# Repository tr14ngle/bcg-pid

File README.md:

# Digitally tuned analog PID controller for BCG system

## Overview

This repository contains KiCad files, as well as some LTSpice simulations for an experimental digitally tuned PID controller. The controller is designed to be part of a ballistocardiography (BCG) measuring system. In BCG, the function of the heart is measured by th forces caused by movement of the blood as a result of heartbeat. This is in contrast to better known electrocardiography (ECG), where heart function is assessed by measuring electrical signals. Compared to ECG, where the shape of the waveform is more important, in BCG the amplitude of the BCG signal carries important information about the heart's condition. Because BCG measures physical force, the patient's mass, among other things, can influence the amplitude of the signal. This makes long-term measurements difficult because the patient's weight and other affecting factors often vary over time. 

This PID controller is a continuation of a project completed Aalto University's Automation and Electrical Engineering Master Programme's Project Work course ([link to project folder](https://wiki.aalto.fi/display/AEEproject/Instrumentation+for+Ballistocardiography+2023?searchId=NLV66OIGJ)). Over the course, a system was implemented where the patient lays on suspended frame. The motion of the suspended frame can be controlled using two solenoids. A load cell is used to measure the position of the frame and a PID controller then controls the solenoids in such a way that the bed frame is kept stationary. This way, when the patient lays motionless, the BCG signal can be aquired from the control signals of the solenoids. This approach keeps the patient's body stationary, effectively canceling body inertia, which normalizes the resultant BCG signal. During the course, an unconventional, analogic PID controller was implemented. The controller was manually tuned using potentiometer which proved unfeasible, as manual tuning was quite diffictult and necessary for each measurement. This project attempts to address this by implementing digital tuning of the P, I and D blocks using digital potentiometers.

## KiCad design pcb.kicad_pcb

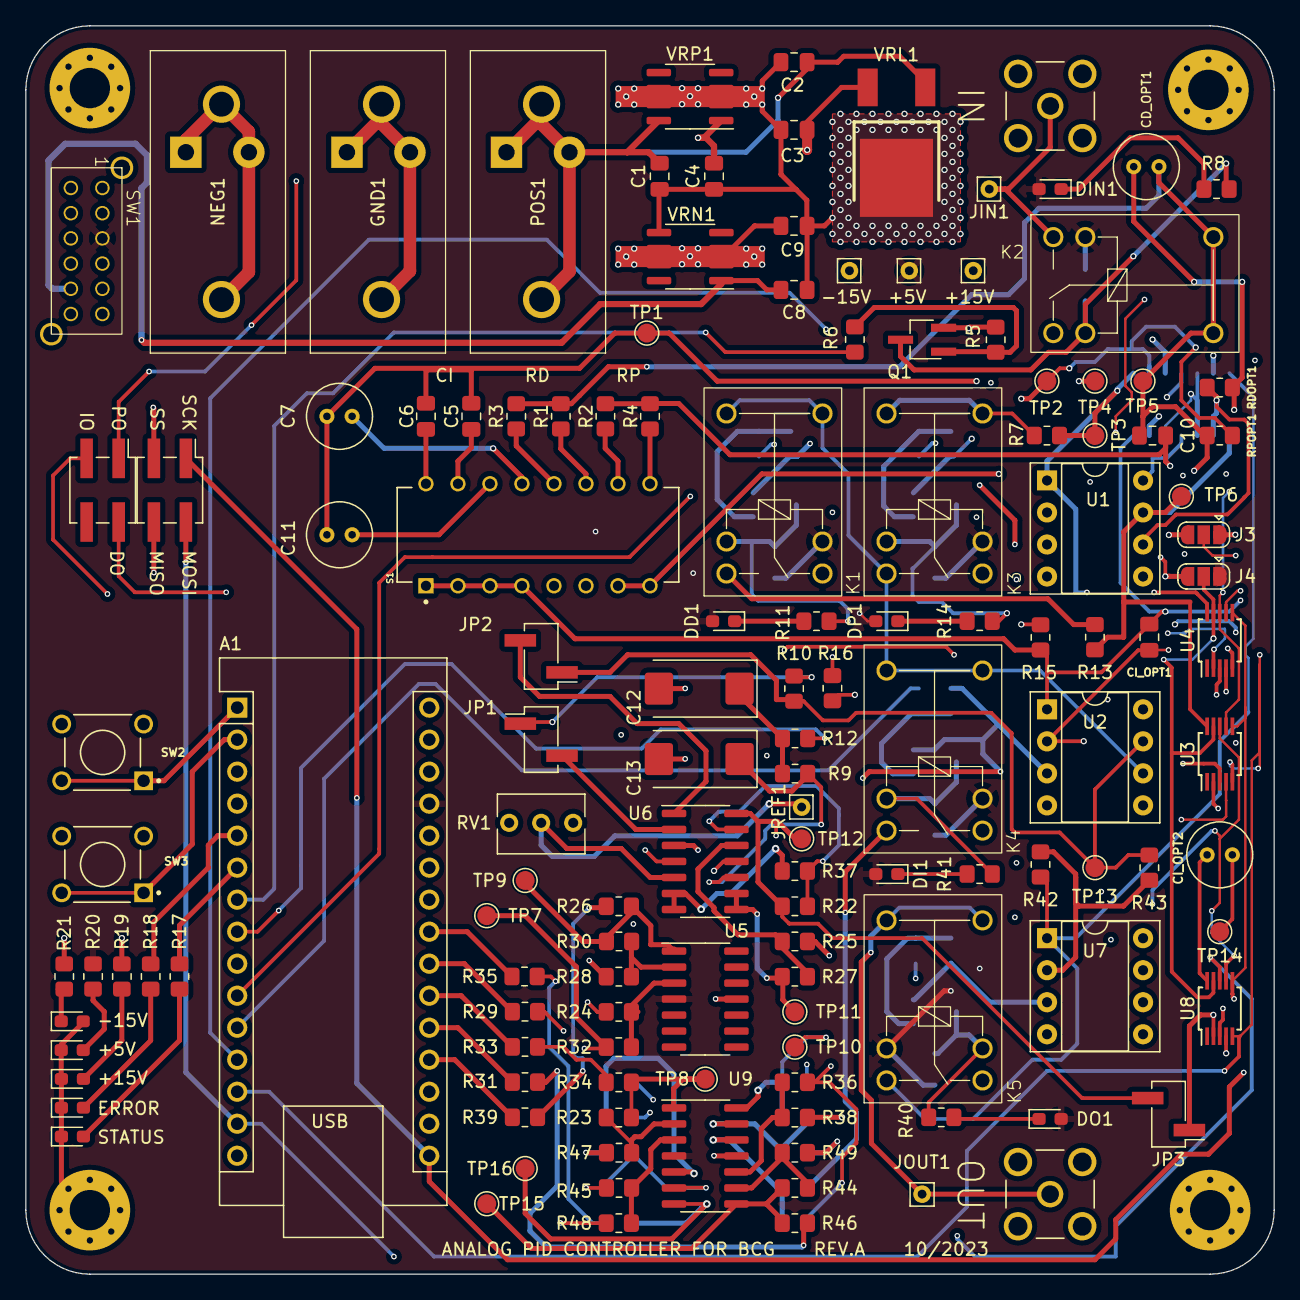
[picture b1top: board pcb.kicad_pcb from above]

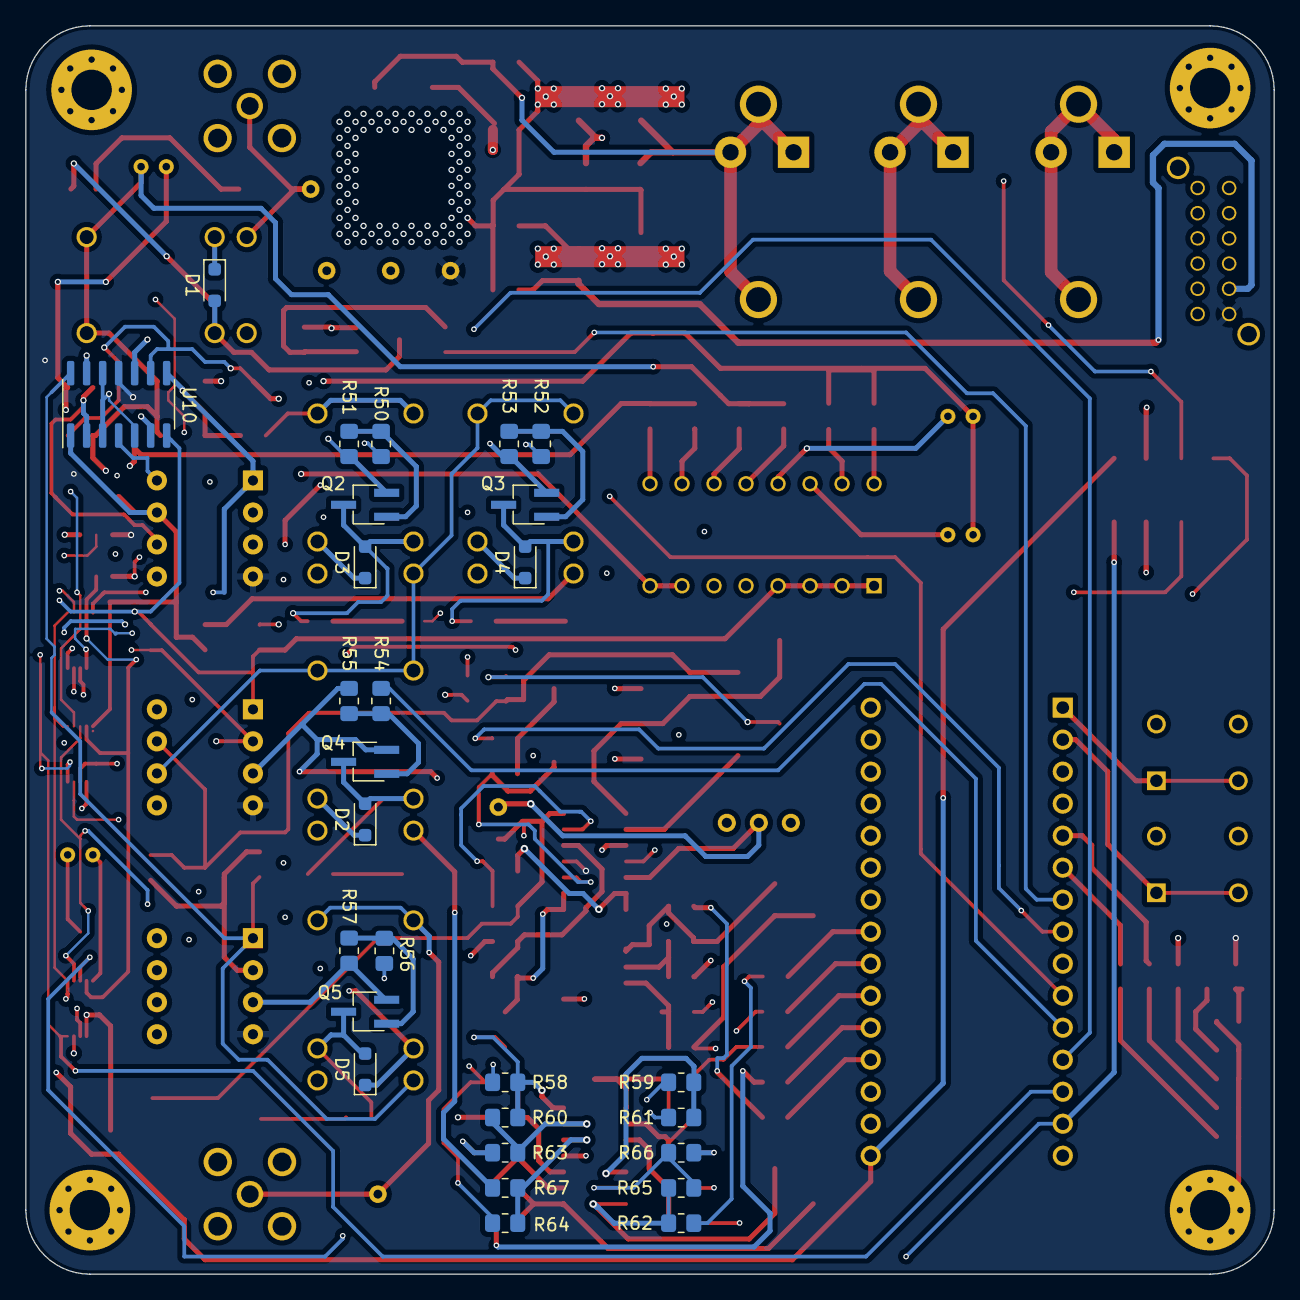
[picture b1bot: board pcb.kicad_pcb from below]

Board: 4 copper layers, 99.1 x 99.1 mm, 170 parts (28 on the bottom side), 109 nets.

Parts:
+1, +2: Conn_01x01_Pin; Pin_D0.7mm_L6.5mm_W1.8mm_FlatFork
-1: Conn_01x01_Pin; Pin_D0.7mm_L6.5mm_W1.8mm_FlatFork
A1: Arduino_Nano_v3.x; Arduino_Nano
C1, C2, C9: 0.33u; C_0805_2012Metric_Pad1.18x1.45mm_HandSolder
C3, C4, C8, C10: 0.1u; C_0805_2012Metric_Pad1.18x1.45mm_HandSolder
C5, C6: C; C_0805_2012Metric_Pad1.18x1.45mm_HandSolder
C7, C11: C; C_Radial_D5.0mm_H5.0mm_P2.00mm
C12, C13: 10u; CP_EIA-7343-40_Kemet-Y_Pad2.25x2.55mm_HandSolder
CD_OPT1: C; C_Radial_D5.0mm_H5.0mm_P2.00mm
CI_OPT1: C; C_0805_2012Metric_Pad1.18x1.45mm_HandSolder
CI_OPT2: C; C_Radial_D5.0mm_H5.0mm_P2.00mm
D1, D2, D3, D4, D5: D; D_SOD-323_HandSoldering
DD1: LED; LED_0603_1608Metric_Pad1.05x0.95mm_HandSolder
DERROR1: LED; LED_0603_1608Metric_Pad1.05x0.95mm_HandSolder
DI1: LED; LED_0603_1608Metric_Pad1.05x0.95mm_HandSolder
DIN1: LED; LED_0603_1608Metric_Pad1.05x0.95mm_HandSolder
DLOG1: LED; LED_0603_1608Metric_Pad1.05x0.95mm_HandSolder
DNEG1: LED; LED_0603_1608Metric_Pad1.05x0.95mm_HandSolder
DO1: LED; LED_0603_1608Metric_Pad1.05x0.95mm_HandSolder
DP1: LED; LED_0603_1608Metric_Pad1.05x0.95mm_HandSolder
DPOS1: LED; LED_0603_1608Metric_Pad1.05x0.95mm_HandSolder
DSTATUS1: LED; LED_0603_1608Metric_Pad1.05x0.95mm_HandSolder
GND1: 24.243.1; 242431
GND_OPT1: Screw_Terminal_01x02; TerminalBlock_RND_205-00276_1x02_P5.00mm_Vertical
H1, H2, H3, H4: MountingHole_Pad; MountingHole_3.2mm_M3_Pad_Via
IN: CONSMA002; LINX_CONSMA002
J1, J2: Conn_02x02_Top_Bottom; PinHeader_2x02_P2.54mm_Vertical_SMD
J3, J4: Conn_01x03_Pin; SolderJumper-3_P1.3mm_Open_RoundedPad1.0x1.5mm
JIN1: Conn_01x01_Pin; Pin_D0.7mm_L6.5mm_W1.8mm_FlatFork
JOUT1: Conn_01x01_Pin; Pin_D0.7mm_L6.5mm_W1.8mm_FlatFork
JP1, JP2, JP3: Jumper_2_Open; PinHeader_1x02_P2.54mm_Vertical_SMD_Pin1Left
JREF1: Conn_01x01_Pin; Pin_D0.7mm_L6.5mm_W1.8mm_FlatFork
K1, K2, K3, K4, K5: SRS-3V
NEG1: 24.243.1; 242431
NEG_OPT1: Screw_Terminal_01x02; TerminalBlock_RND_205-00276_1x02_P5.00mm_Vertical
OUT: CONSMA002; LINX_CONSMA002
POS1: 24.243.1; 242431
POS_OPT1: Screw_Terminal_01x02; TerminalBlock_RND_205-00276_1x02_P5.00mm_Vertical
Q1, Q2, Q3, Q4, Q5: NMOS; TSOT-23_HandSoldering
R1, R2, R3, R4: R; R_0805_2012Metric_Pad1.20x1.40mm_HandSolder
R5, R51, R53, R55, R57: 47k; R_0805_2012Metric_Pad1.20x1.40mm_HandSolder
R6, R50, R52, R54, R56: 470; R_0805_2012Metric_Pad1.20x1.40mm_HandSolder
R7, R10, R13, R15, R42, R43: 10k; R_0805_2012Metric_Pad1.20x1.40mm_HandSolder
R8, R11, R14, R16, R17, R18, R20, R29, R31, R33, R35, R39, R40, R41: 330; R_0805_2012Metric_Pad1.20x1.40mm_HandSolder
R9, R12: 68; R_0805_2012Metric_Pad1.20x1.40mm_HandSolder
R19, R21: 1.2k; R_0805_2012Metric_Pad1.20x1.40mm_HandSolder
R22, R25, R26, R28, R32, R34, R38, R46, R47, R48, R49, R58, R61, R62, R63, R66, R67: 100k; R_0805_2012Metric_Pad1.20x1.40mm_HandSolder
R23, R24, R30, R36, R44, R45, R59, R60, R64, R65: 15k; R_0805_2012Metric_Pad1.20x1.40mm_HandSolder
R27, R37: 18k; R_0805_2012Metric_Pad1.20x1.40mm_HandSolder
RDOPT1: 10k; R_0805_2012Metric_Pad1.20x1.40mm_HandSolder
RPOPT1: 10k; R_0805_2012Metric_Pad1.20x1.40mm_HandSolder
RV1: 100k; Potentiometer_Bourns_3266Y_Vertical
S1: ADE0804; SW_ADE0804
SW1: EG4208
SW2, SW3: 1825910-6; SW_1825910-6-4
TP1, TP2, TP3, TP4, TP5, TP6, TP7, TP8, TP9, TP10, TP11, TP12, TP13, TP14, TP15, TP16: TestPoint; TestPoint_Pad_D1.5mm
U1, U2, U7: LM358; DIP-8_W7.62mm_Socket
U3, U4, U8: AD5290; MSOP-10_3x3mm_P0.5mm
U5, U6, U9, U10: NCS20074D; SOIC-14_3.9x8.7mm_P1.27mm
VRL1: NCV7805BDTRKG; NCV7805BDTRKG_1
VRN1: MC79L15_SO8; SOIC-8_3.9x4.9mm_P1.27mm
VRP1: MC78L15_SO8; SOIC-8_3.9x4.9mm_P1.27mm

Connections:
2.5V: JREF1.1, R24.1, R36.1, R45.1, R59.1, R64.1, RV1.2, U6.5 (+)
+5V: +2.1, A1.27 (+5V), D1.1 (K), D2.1 (K), D3.1 (K), D4.1 (K), D5.1 (K), DD1.2 (A), DI1.2 (A), DIN1.2 (A), DO1.2 (A), DP1.2 (A), J4.1, K1.3, K2.4, K3.3, K4.3, K5.4, R20.2, SW1.3, U5.4 (V+), U9.4 (V+)
+15V: +1.1, J4.3, R19.2, SW1.6, U1.8 (V+), U2.8 (V+), U6.4 (V+), U7.8 (V+), U10.4 (V+)
-15V: -1.1, J3.3, R21.2, SW1.12, U1.4 (V-), U2.4 (V-), U6.11 (V-), U7.4 (V-), U10.11 (V-)
/Ci1: C5.1, C6.1, C7.1, C11.1, CI_OPT1.1, CI_OPT2.1, TP1.1, U2.2 (-), U8.10 (RW), U10.6 (-)
/Ci2: CI_OPT1.2, CI_OPT2.2, R15.1, S1.1, S1.2, S1.3, S1.4, TP14.1, U2.1, U10.7
/K1D: D3.2 (A), K3.4, Q2.1 (D), R14.1
/K2D: D2.2 (A), K4.4, Q4.1 (D), R41.1
/K3D: D4.2 (A), K1.4, Q3.1 (D), R11.1
/K4D: D5.2 (A), K5.3, Q5.1 (D), R40.1
/K5D: D1.2 (A), K2.3, Q1.1 (D), R8.1
/Rd1: C10.2, CD_OPT1.2, R2.2, R4.2, RDOPT1.1
/Rd2: RDOPT1.2, S1.7, S1.8, TP4.1, U1.6 (-), U3.2 (RL), U10.2 (-)
/Rp1: C10.1, CD_OPT1.1, JP3.1 (A), K2.5, K2.6, R1.2, R3.2, R38.1, RPOPT1.1, TP5.1, U8.2 (RL)
/Rp2: RPOPT1.2, S1.5, S1.6, TP2.1, U1.2 (-), U4.2 (RL), U10.9 (-)
/control_out: A1.8 (D5), R12.2
/der_out: R13.1, TP6.1, U1.7, U3.10 (RW), U10.1
/inv_in: R42.1, R43.2, U7.2 (-), U10.13 (-)
/inv_out: K5.1, R32.1, R42.2, TP7.1, U7.1, U10.14
/potvdd: J4.2, U3.9 (Vdd+), U4.9 (Vdd+), U8.9 (Vdd+)
/potvss: J3.2, U3.3 (Vss-), U4.3 (Vss-), U8.3 (Vss-)
/prop_out: R7.1, TP3.1, U1.1, U4.10 (RW), U10.8
/sig_d: K1.1, R13.2, R61.1
/sig_i: K4.1, R15.2, R67.1
/sig_p: K3.5, K3.6, R7.2, R48.1
/sum_in: JP1.1 (A), K1.5, K1.6, K3.1, K4.5, K4.6, R10.1, U2.6 (-)
/sum_out: JP2.1 (A), R10.2, R43.1, TP13.1, U2.7
DO: J2.2, U3.8 (SDO), U8.7 (SDI)
GND: A1.4 (GND), A1.29 (GND), C1.1, C2.1, C3.1, C4.1, C8.2, C9.2, C12.2, C13.2, DERROR1.1 (K), DLOG1.1 (K), DNEG1.2 (A), DPOS1.1 (K), DSTATUS1.1 (K), GND1.1, GND1.2, GND_OPT1.1, GND_OPT1.2, H1.1, H2.1, H3.1, H4.1, IN.S1, IN.S2, IN.S3, IN.S4, J3.1, OUT.S1, OUT.S2, OUT.S3, OUT.S4, Q1.3 (S), Q2.3 (S), Q3.3 (S), Q4.3 (S), Q5.3 (S), R5.1, R25.1, R28.1, R47.1, R49.1, R51.1, R53.1, R55.1, R57.1, R63.1, R66.1, RV1.3, SW1.13 (GND), SW1.14 (GND), SW2.3, SW2.4, SW3.3, SW3.4, U1.3 (+), U1.5 (+), U2.3 (+), U2.5 (+), U3.4 (GND), U4.4 (GND), U5.11 (V-), U6.3 (+), U7.3 (+), U8.4 (GND), U9.11 (V-), U10.3 (+), U10.5 (+), U10.10 (+), U10.12 (+), VRL1.3 (GROUND), VRN1.5 (GND), VRP1.2 (GND), VRP1.3 (GND), VRP1.6 (GND), VRP1.7 (GND)
IO: J2.3, U8.8 (SDO)
MISO: A1.15 (D12), J1.4
MOSI: A1.14 (D11), J1.2, U4.7 (SDI)
unnamed: A1.19 (A0), R39.1
unnamed: A1.20 (A1), R31.2
unnamed: A1.21 (A2), R33.2
unnamed: A1.22 (A3), R29.2
unnamed: A1.23 (A4), R35.2
unnamed: A1.2 (D0/RX), SW3.1, SW3.2
unnamed: A1.1 (D1/TX), SW2.1, SW2.2
unnamed: A1.5 (D2), R18.2
unnamed: A1.6 (D3), R17.2
unnamed: A1.7 (D4), R6.2
unnamed: A1.9 (D6), R56.2
unnamed: A1.10 (D7), R52.2
unnamed: A1.11 (D8), R54.2
unnamed: A1.12 (D9), R50.2
unnamed: C6.2, S1.1-1
unnamed: C5.2, S1.2-1
unnamed: C11.2, S1.3-1
unnamed: C7.2, S1.4-1
unnamed: C12.1, R9.2, R12.1
unnamed: DD1.1 (K), R11.2
unnamed: DERROR1.2 (A), R18.1
unnamed: DI1.1 (K), R41.2
unnamed: DIN1.1 (K), R8.2
unnamed: DLOG1.2 (A), R20.1
unnamed: DNEG1.1 (K), R21.1
unnamed: DO1.1 (K), R40.2
unnamed: DP1.1 (K), R14.2
unnamed: DPOS1.2 (A), R19.1
unnamed: DSTATUS1.2 (A), R17.1
unnamed: IN.1, JIN1.1, K2.1
unnamed: R37.2, U6.6 (-), U6.7
unnamed: JOUT1.1, K5.5, K5.6, OUT.1
unnamed: JP1.2 (B), U6.2 (-)
unnamed: JP2.2 (B), U6.1
unnamed: JP3.2 (B), R16.1, R22.1, TP12.1, U6.14
unnamed: K2.2, R16.2
unnamed: C9.1, NEG1.1, NEG1.2, NEG_OPT1.1, NEG_OPT1.2, VRN1.2 (IN), VRN1.3 (IN), VRN1.6 (IN), VRN1.7 (IN)
unnamed: C1.2, C2.2, POS1.1, POS1.2, POS_OPT1.1, POS_OPT1.2, VRL1.1 (INPUT), VRP1.8 (IN)
unnamed: Q2.2 (G), R50.1, R51.2
unnamed: Q4.2 (G), R54.1, R55.2
unnamed: Q3.2 (G), R52.1, R53.2
unnamed: Q5.2 (G), R56.1, R57.2
unnamed: Q1.2 (G), R5.2, R6.1
unnamed: R1.1, S1.6-1
unnamed: R3.1, S1.5-1
unnamed: R2.1, S1.7-1
unnamed: R4.1, S1.8-1
unnamed: R23.1, R34.1, TP8.1, U9.1
unnamed: R26.2, R39.2
unnamed: R31.1, R46.2
unnamed: R33.1, R34.2
unnamed: R29.1, R58.2
unnamed: R35.1, R62.2
unnamed: R44.1, R46.1, TP15.1, U9.8
unnamed: R62.1, R65.1, TP16.1, U9.7
unnamed: R58.1, R60.1, TP10.1, U9.14
unnamed: R26.1, R30.1, TP9.1, U5.1
unnamed: C13.1, R9.1, U6.10 (+)
unnamed: R27.2, TP11.1, U6.8, U6.9 (-)
unnamed: R25.2, R27.1, U6.12 (+)
unnamed: R22.2, R37.1, U6.13 (-)
unnamed: R45.2, R48.2, U9.3 (+)
unnamed: R23.2, R47.2, U9.2 (-)
unnamed: R59.2, R61.2, U9.5 (+)
unnamed: R65.2, R66.2, U9.6 (-)
unnamed: R36.2, R38.2, U9.10 (+)
unnamed: R44.2, R49.2, U9.9 (-)
unnamed: R64.2, R67.2, U9.12 (+)
unnamed: R60.2, R63.2, U9.13 (-)
unnamed: R24.2, R32.2, U5.3 (+)
unnamed: R28.2, R30.2, U5.2 (-)
unnamed: C3.2, SW1.2, VRL1.2 (OUTPUT)
unnamed: C8.1, SW1.11, VRN1.1 (OUT)
unnamed: C4.2, SW1.5, VRP1.1 (OUT)
PO: J2.1, U3.7 (SDI), U4.8 (SDO)
SCK: A1.16 (D13), J1.1, U3.6 (CLK), U4.6 (CLK), U8.6 (CLK)
SS: A1.13 (D10), J1.3, U3.5 (~CS), U4.5 (~CS), U8.5 (~CS)

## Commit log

2025-01-03 Create relay_test
